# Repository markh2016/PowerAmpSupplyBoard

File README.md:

# PowerAmpSupplyBoard

Amplifier  supply board  design for  25watts amplifiers 
would  suite subwooofer amp  for base in  home or similar
all files included 
Software used  for this KICAD  version 5.1 

Enjoy

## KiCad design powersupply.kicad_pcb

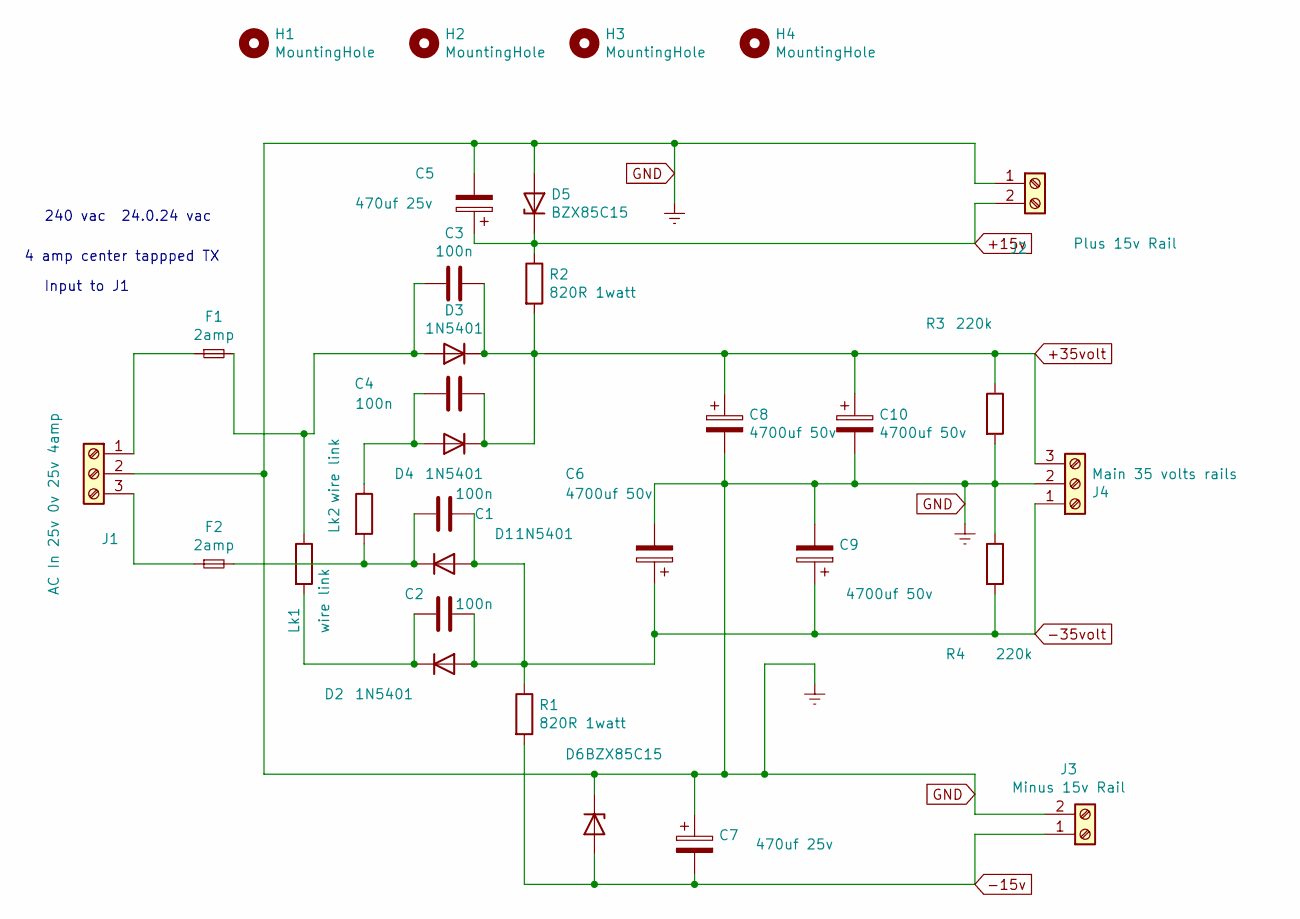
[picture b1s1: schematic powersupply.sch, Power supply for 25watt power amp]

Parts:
C1, C2, C3, C4: 100n; C_Disc_D3.4mm_W2.1mm_P2.50mm
C5, C7: 470uf 25v; CP_Radial_D5.0mm_P2.00mm
C6, C8, C9, C10: 4700uf 50v; CP_Radial_D25.0mm_P10.00mm_SnapIn
D1, D2, D3, D4: 1N5401; D_DO-201AD_P15.24mm_Horizontal
D5, D6: BZX85C15; D_DO-41_SOD81_P10.16mm_Horizontal
F1, F2: 2amp; Fuseholder_Cylinder-5x20mm_Schurter_0031_8201_Horizontal_Op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
H1, H2, H3, H4: MountingHole; MountingHole_2.7mm
J1: AC In 25v 0v 25v 4amp; TerminalBlock_Phoenix_MKDS-1,5-3-5.08_1x03_P5.08mm_Horizont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
J2: Plus 15v Rail; TerminalBlock_Phoenix_MKDS-1,5-2_1x02_P5.00mm_Horizontal
J3: Minus 15v Rail; TerminalBlock_Phoenix_MKDS-1,5-2_1x02_P5.00mm_Horizontal
J4: Main 35 volts rails; TerminalBlock_Phoenix_MKDS-1,5-3-5.08_1x03_P5.08mm_Horizont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
Lk1, Lk2: wire link; R_Axial_DIN0204_L3.6mm_D1.6mm_P7.62mm_Horizontal
R1, R2: 820R 1watt; R_Axial_DIN0411_L9.9mm_D3.6mm_P20.32mm_Horizontal
R3, R4: 220k; R_Axial_DIN0309_L9.0mm_D3.2mm_P15.24mm_Horizontal

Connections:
+15v: C5.1, D5.1 (K), J2.2, R2.1
+35volt: C3.1, C4.1, C8.1, C10.1, D3.1 (K), D4.1 (K), J4.3, R2.2, R3.1
-15v: C7.2, D6.2 (A), J3.1, R1.2
-35volt: C1.1, C2.1, C6.1, C9.1, D1.2 (A), D2.2 (A), J4.1, R1.1, R4.2
GND: C5.2, C6.2, C7.1, C8.2, C9.2, C10.2, D5.2 (A), D6.1 (K), J1.2, J2.1, J3.2, J4.2, R3.2, R4.1
unnamed: C1.2, D1.1 (K), F2.2, Lk2.2
unnamed: C2.2, D2.1 (K), Lk1.2
unnamed: C3.2, D3.2 (A), F1.2, Lk1.1
unnamed: C4.2, D4.2 (A), Lk2.1
unnamed: F1.1, J1.1
unnamed: F2.1, J1.3

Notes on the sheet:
240 vac 24.0.24 vac
4 amp center tappped TX
Input to J1

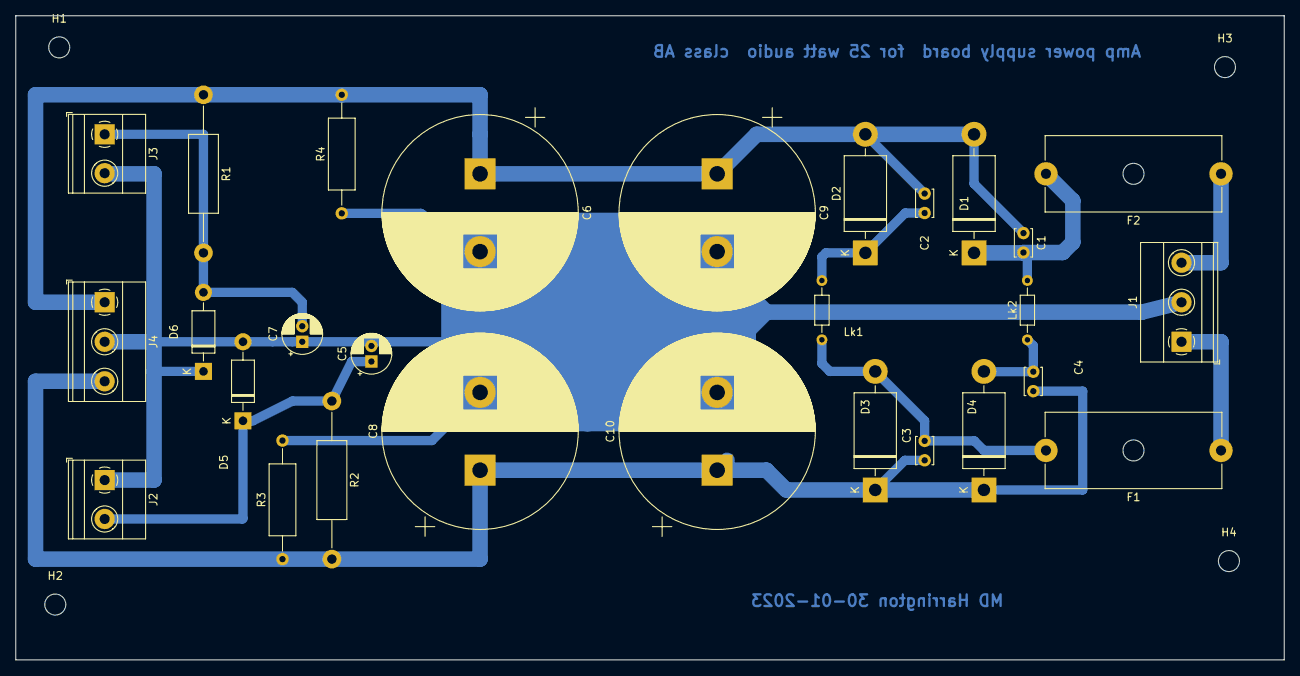
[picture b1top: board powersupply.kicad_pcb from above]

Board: 2 copper layers, 163.1 x 82.8 mm, 32 parts (0 on the bottom side), 11 nets.

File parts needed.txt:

Reference, Value, Footprint, Datasheet
"D3","1N5401","Diode_THT:D_DO-201AD_P15.24mm_Horizontal","http://www.vishay.com/docs/88516/1n5400.pdf"
"D4","1N5401","Diode_THT:D_DO-201AD_P15.24mm_Horizontal","http://www.vishay.com/docs/88516/1n5400.pdf"
"D1","1N5401","Diode_THT:D_DO-201AD_P15.24mm_Horizontal","http://www.vishay.com/docs/88516/1n5400.pdf"
"D2","1N5401","Diode_THT:D_DO-201AD_P15.24mm_Horizontal","http://www.vishay.com/docs/88516/1n5400.pdf"
"J1","Screw_Terminal_01x03","TerminalBlock_Phoenix:TerminalBlock_Phoenix_MKDS-1,5-3-5.08_1x03_P5.08mm_Horizontal","~"
"C8","4700uf 50v","Capacitor_THT:CP_Radial_D25.0mm_P10.00mm_SnapIn","~"
"C10","4700uf 50v","Capacitor_THT:CP_Radial_D25.0mm_P10.00mm_SnapIn","~"
"C6","4700uf 50v","Capacitor_THT:CP_Radial_D25.0mm_P10.00mm_SnapIn","~"
"C9","4700uf 50v","Capacitor_THT:CP_Radial_D25.0mm_P10.00mm_SnapIn","~"
"R2","820R 1watt","Resistor_THT:R_Axial_DIN0411_L9.9mm_D3.6mm_P20.32mm_Horizontal","~"
"R1","820R 1watt","Resistor_THT:R_Axial_DIN0411_L9.9mm_D3.6mm_P20.32mm_Horizontal","~"
"D5","BZX85C15","Diode_THT:D_DO-41_SOD81_P10.16mm_Horizontal","https://www.vishay.com/docs/85816/1n4728a.pdf"
"D6","BZX85C15","Diode_THT:D_DO-41_SOD81_P10.16mm_Horizontal","https://www.vishay.com/docs/85816/1n4728a.pdf"
"C5","470uf 25v","Capacitor_THT:CP_Radial_D5.0mm_P2.00mm","~"
"C7","470uf 25v","Capacitor_THT:CP_Radial_D5.0mm_P2.00mm","~"
"F1","2amp","Fuse:Fuseholder_Cylinder-5x20mm_Schurter_0031_8201_Horizontal_Open","~"
"F2","2amp","Fuse:Fuseholder_Cylinder-5x20mm_Schurter_0031_8201_Horizontal_Open","~"
"C3","100n","Capacitor_THT:C_Disc_D3.4mm_W2.1mm_P2.50mm","~"
"C4","100n","Capacitor_THT:C_Disc_D3.4mm_W2.1mm_P2.50mm","~"
"C1","100n","Capacitor_THT:C_Disc_D3.4mm_W2.1mm_P2.50mm","~"
"C2","100n","Capacitor_THT:C_Disc_D3.4mm_W2.1mm_P2.50mm","~"
"J3","Screw_Terminal_01x02","TerminalBlock_Phoenix:TerminalBlock_Phoenix_MKDS-1,5-2_1x02_P5.00mm_Horizontal","~"
"J2","Screw_Terminal_01x02","TerminalBlock_Phoenix:TerminalBlock_Phoenix_MKDS-1,5-2_1x02_P5.00mm_Horizontal","~"
"J4","Screw_Terminal_01x03","TerminalBlock_Phoenix:TerminalBlock_Phoenix_MKDS-1,5-3-5.08_1x03_P5.08mm_Horizontal","~"
"H1","MountingHole","MountingHole:MountingHole_2.7mm","~"
"H2","MountingHole","MountingHole:MountingHole_2.7mm","~"
"H3","MountingHole","MountingHole:MountingHole_2.7mm","~"
"H4","MountingHole","MountingHole:MountingHole_2.7mm","~"
"R3","220k","Resistor_THT:R_Axial_DIN0309_L9.0mm_D3.2mm_P15.24mm_Horizontal","~"
"R4","220k","Resistor_THT:R_Axial_DIN0309_L9.0mm_D3.2mm_P15.24mm_Horizontal","~"
